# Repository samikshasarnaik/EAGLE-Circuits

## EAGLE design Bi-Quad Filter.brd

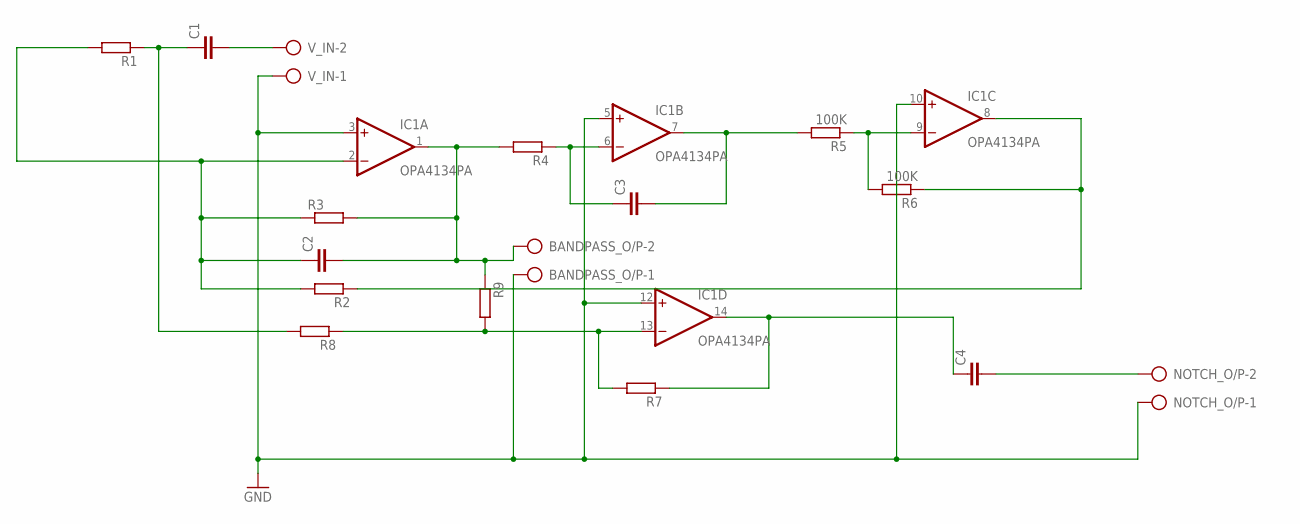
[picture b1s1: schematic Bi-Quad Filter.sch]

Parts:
BANDPASS_O/P: AK300/2
C1, C2, C3, C4: C-EU050-024X044; C050-024X044
IC1: OPA4134PA; DIL14
NOTCH_O/P: AK300/2
R1, R2, R3, R4, R7, R8, R9: R-EU_0204/5; 0204/5
R5, R6: 100K; 0204/5
V_IN: AK300/2

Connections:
GND: BANDPASS_O/P.1, IC1.3 (+IN), IC1.5 (+IN), IC1.10 (+IN), IC1.12 (+IN), NOTCH_O/P.1, V_IN.1
unnamed: C1.2, V_IN.2
unnamed: C1.1, R1.1, R8.2
unnamed: C2.1, IC1.2 (-IN), R1.2, R2.2, R3.1
unnamed: IC1.8 (OUT), R2.1, R6.1
unnamed: C3.1, IC1.6 (-IN), R4.1
unnamed: BANDPASS_O/P.2, C2.2, IC1.1 (OUT), R3.2, R4.2, R9.1
unnamed: IC1.9 (-IN), R5.1, R6.2
unnamed: C3.2, IC1.7 (OUT), R5.2
unnamed: IC1.13 (-IN), R7.2, R8.1, R9.2
unnamed: C4.1, IC1.14 (OUT), R7.1
unnamed: C4.2, NOTCH_O/P.2
V+: IC1.4 (V+)
V-: IC1.11 (V-)

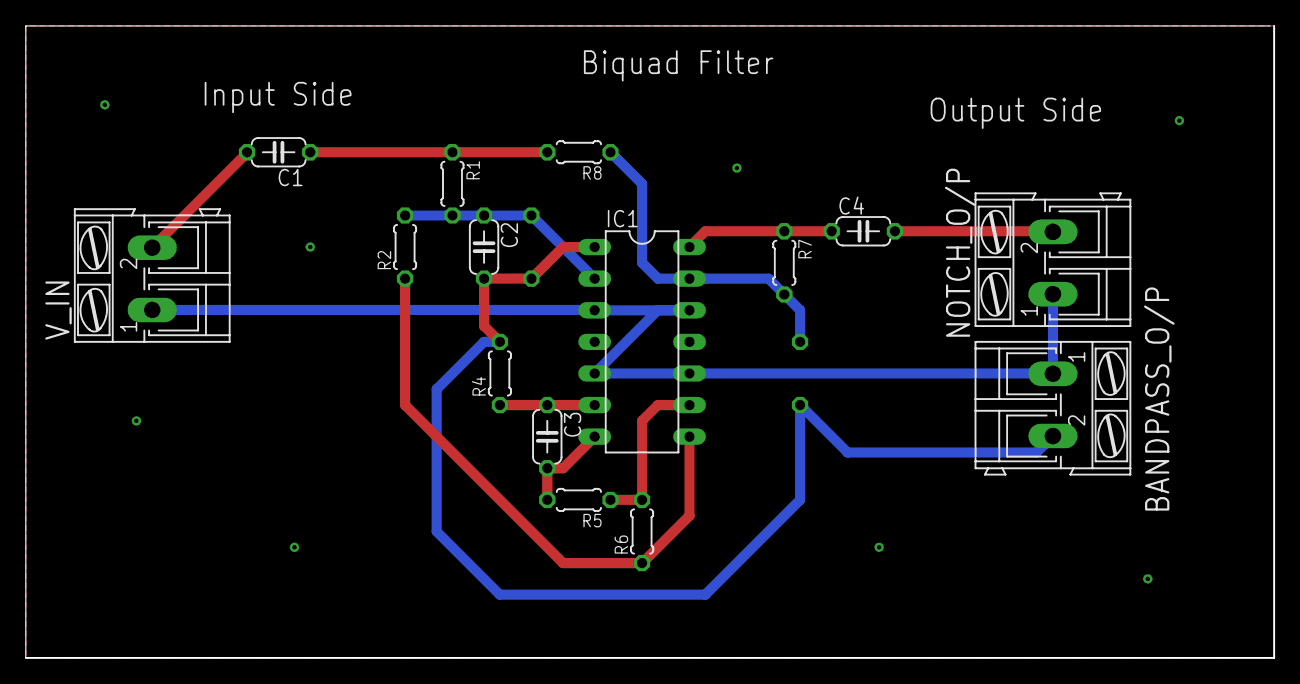
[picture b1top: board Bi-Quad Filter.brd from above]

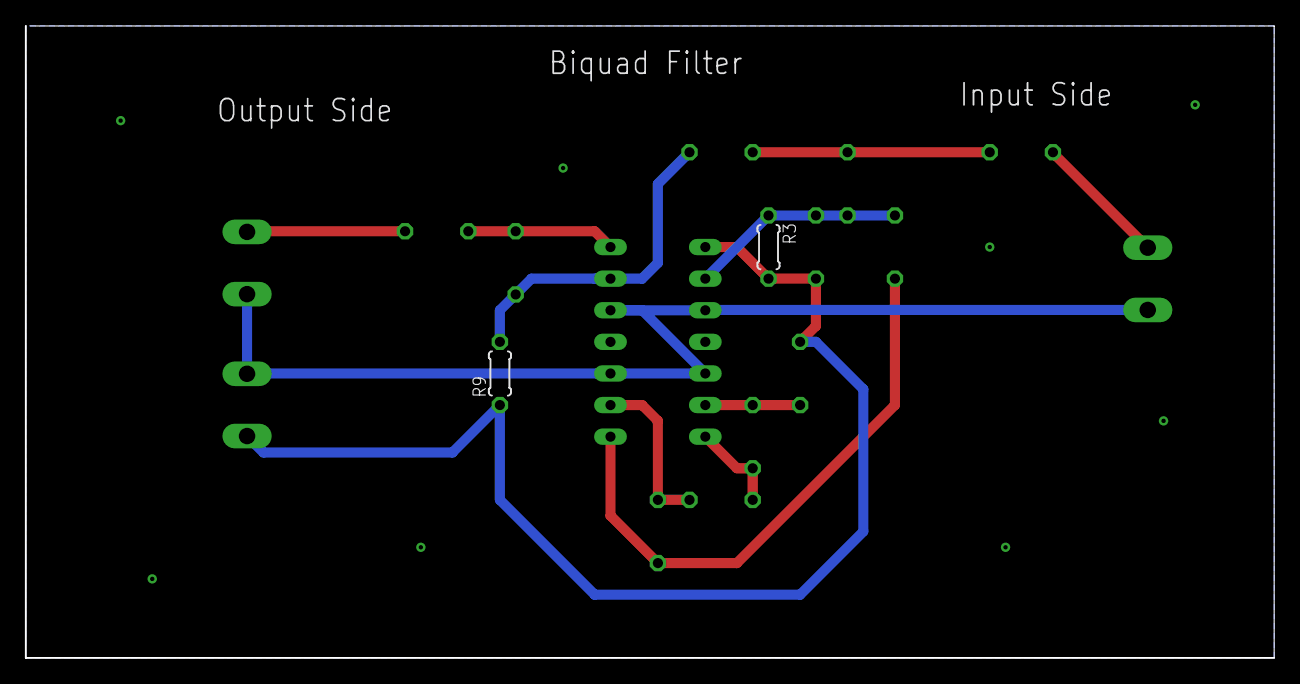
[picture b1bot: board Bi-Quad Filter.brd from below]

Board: 2 copper layers, 100.3 x 50.8 mm, 17 parts (2 on the bottom side), 12 nets.
